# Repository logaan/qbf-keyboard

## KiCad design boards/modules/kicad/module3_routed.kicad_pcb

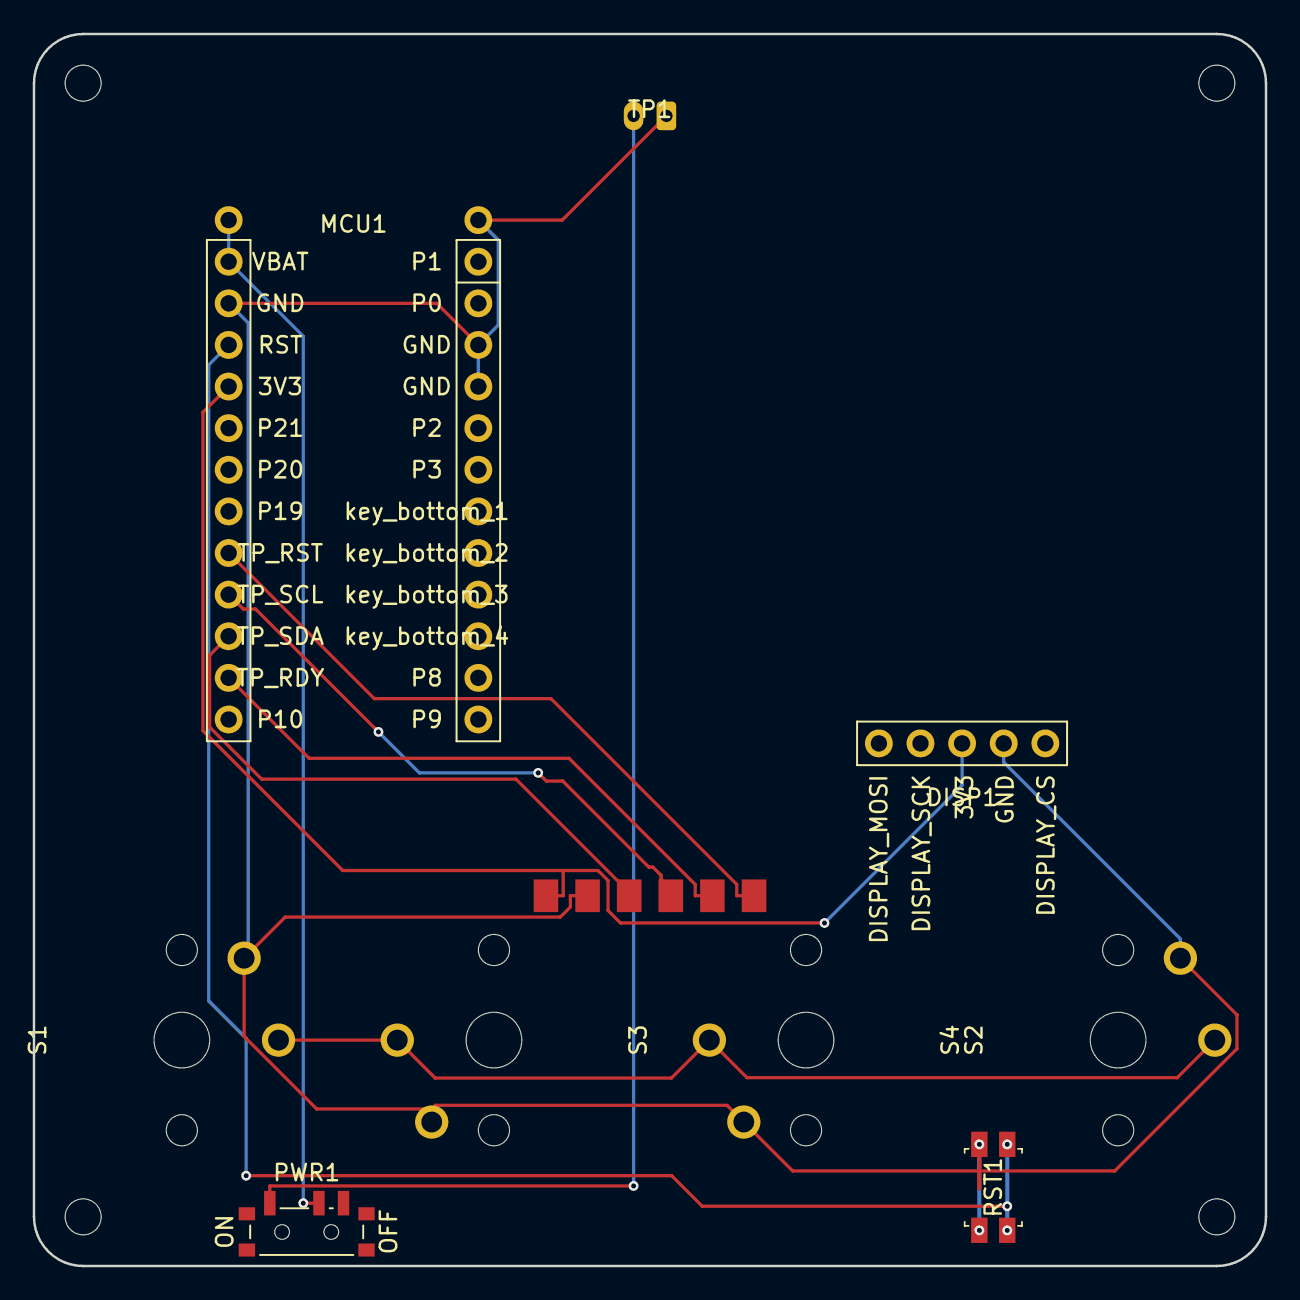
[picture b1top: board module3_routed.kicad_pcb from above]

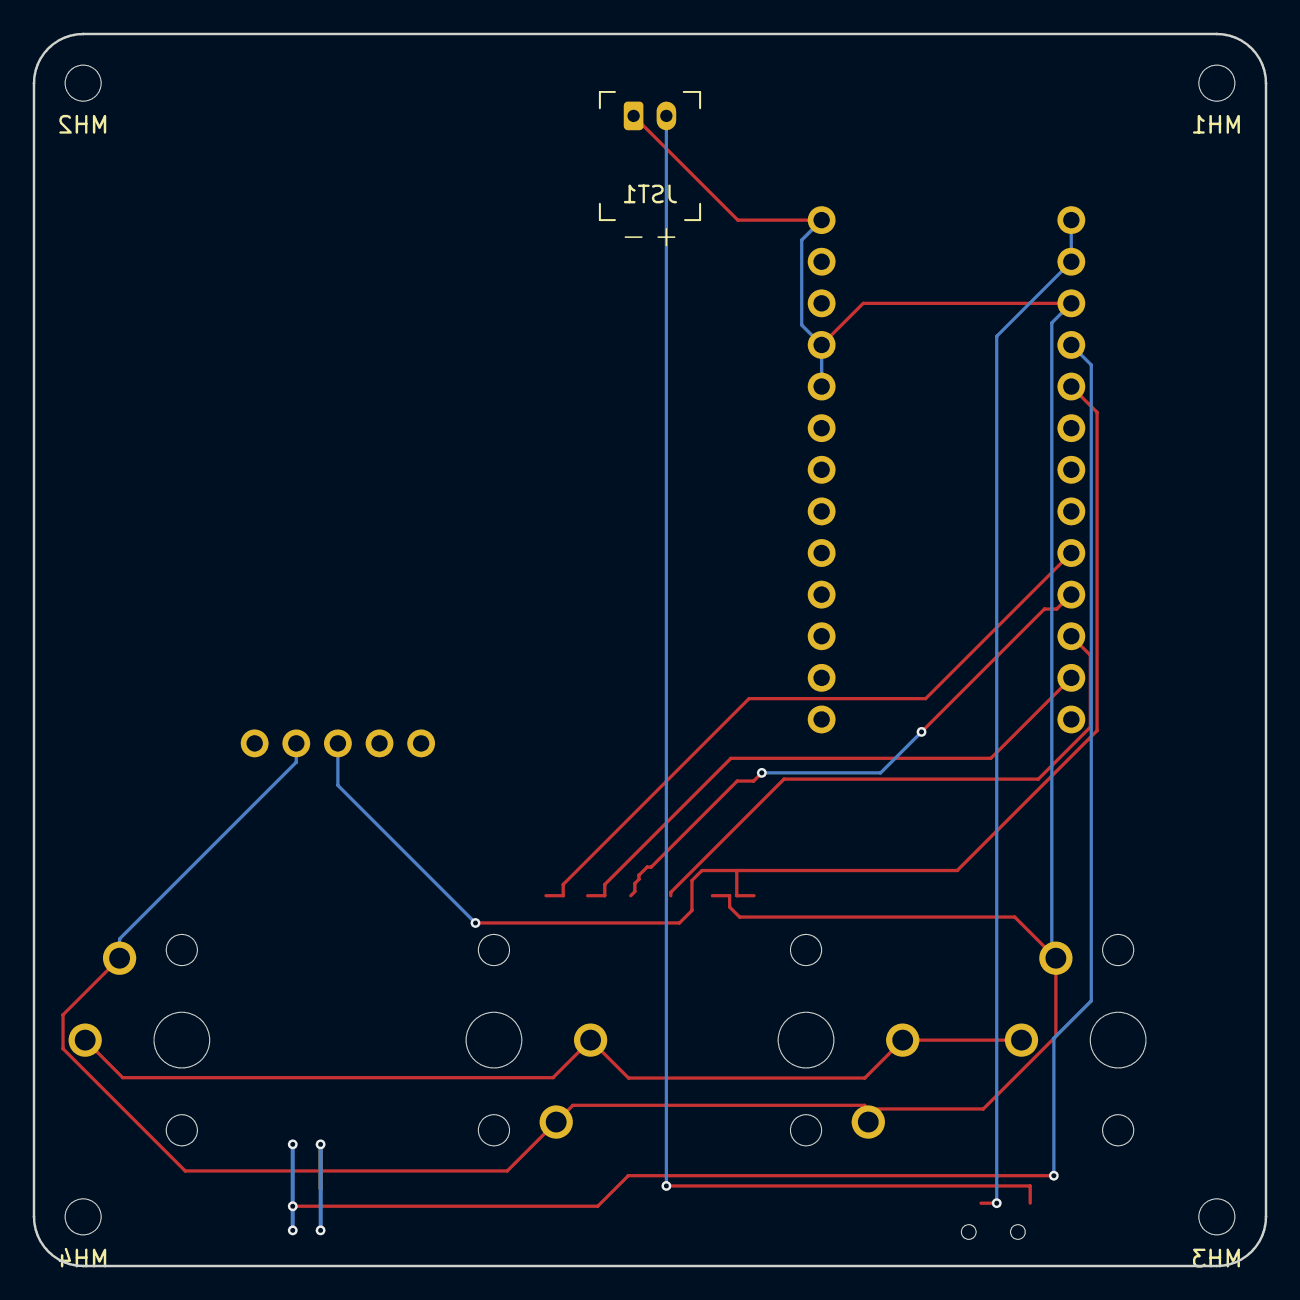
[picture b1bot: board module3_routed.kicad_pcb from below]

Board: 2 copper layers, 75.2 x 75.2 mm, 14 parts (5 on the bottom side), 10 nets.

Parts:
DISP1: display_nice_view
JST1: battery_connector_jst_ph_2
MCU1: mcu_nice_nano
MH1, MH2, MH3, MH4: mounting_hole_npth
PWR1: power_switch_smd_side
RST1: reset_switch_smd_side
S1, S2, S3, S4: switch_choc_v1_v2
TP1: TPS43_abstract_interface

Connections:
3V3: DISP1.3, MCU1.21, TP1.1
BAT_P: JST1.2, PWR1.1
GND: DISP1.4, JST1.1, MCU1.3, MCU1.4, MCU1.23, MCU1.26, RST1.1, RST1.3, S1.1, S2.1, S3.1, S4.1, TP1.2
RST: MCU1.22, RST1.2, RST1.4
TP_RDY: MCU1.14, TP1.5
TP_RST: MCU1.17, TP1.6
TP_SCL: MCU1.16, TP1.4
TP_SDA: MCU1.15, TP1.3
VBAT: MCU1.24, MCU1.25, PWR1.2
default_default: S1.2, S2.2, S3.2, S4.2

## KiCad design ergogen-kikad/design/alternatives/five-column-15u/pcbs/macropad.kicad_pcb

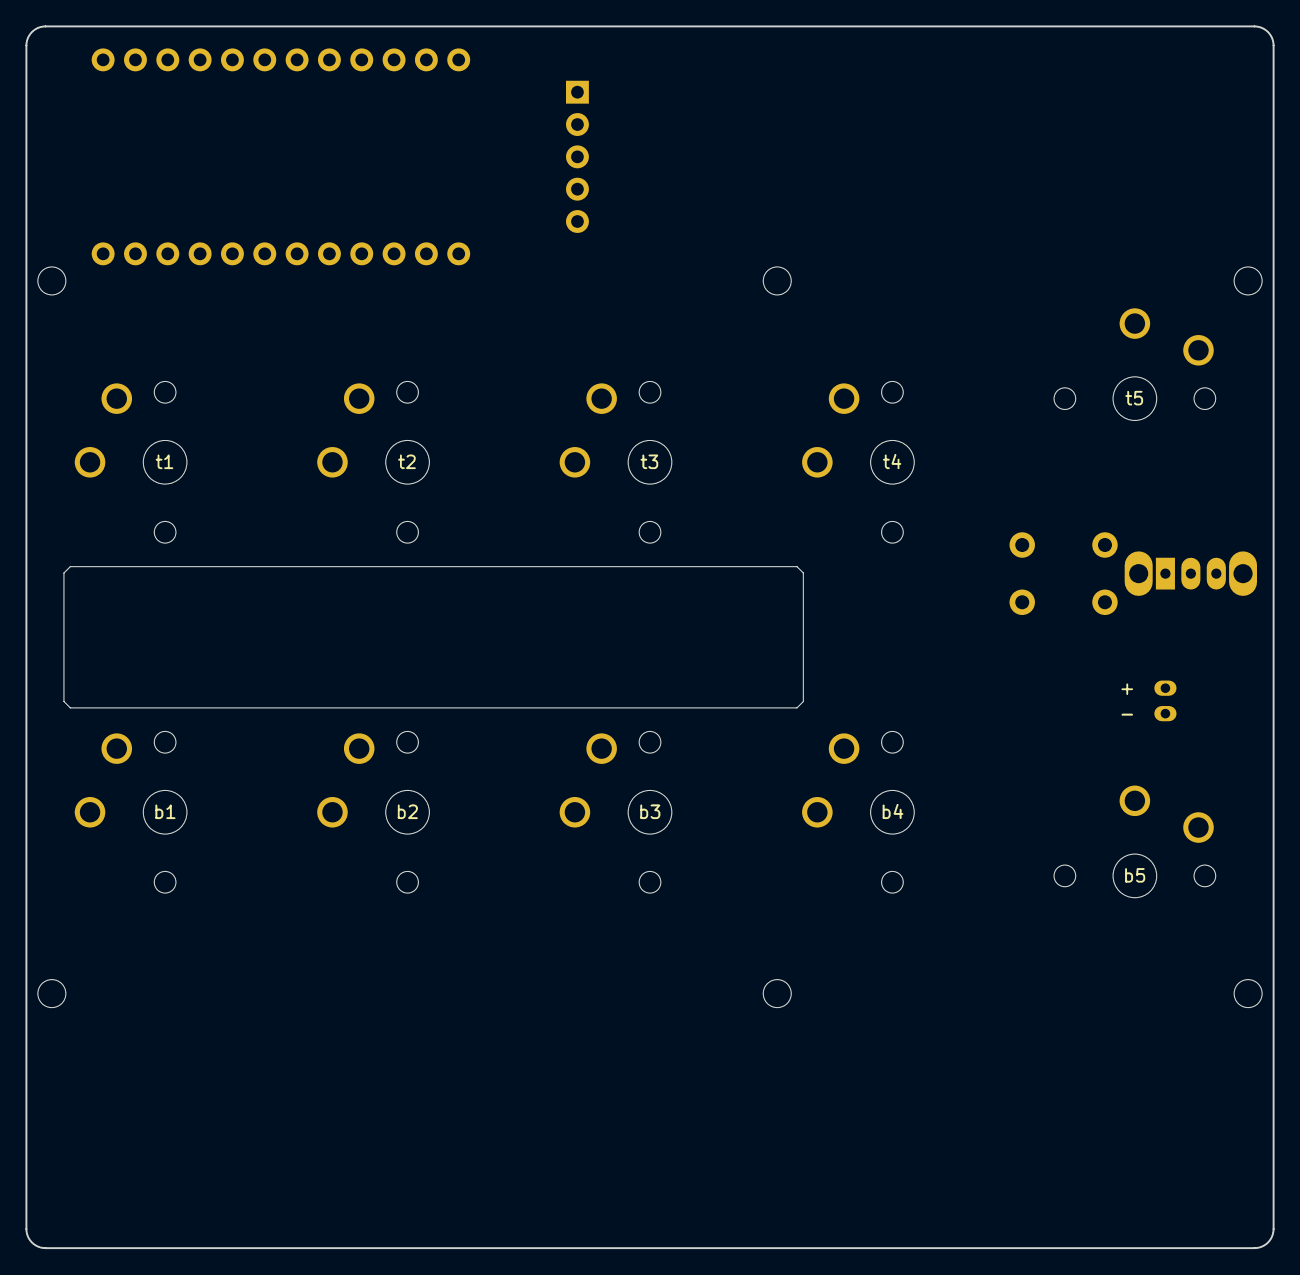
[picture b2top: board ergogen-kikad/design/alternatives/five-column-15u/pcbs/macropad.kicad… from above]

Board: 2 copper layers, 98.0 x 96.0 mm, 23 parts (0 on the bottom side), 18 nets, no tracks yet.

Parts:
BAT1: 301055 220mAh max 57.5x10.5x3.5 z=-1.4; Protected_301055_Battery_Envelope
H1, H2, H3, H4, H5, H6: M2 mount; M2_Mount
J1: JST-PH S2B-PH-K-S; JST_PH_S2B_PH_K_Horizontal
LCD1: nice!view; Nice_View_Socketed_Module
MCU1: nice!nano v2; Nice_Nano_V2
PWR1: OS102011MS2QN1; CK_OS102011MS2QN1
RST1: 6mm top-actuated tactile; SW_PUSH_6mm_H4_3mm
S1, S2, S3, S4, S5, S6, S7, S8: Choc v1 1.5U; PG1350_1_5U
S9, S10: Choc v1 1U; PG1350_1U
WELL1: Battery well 58.1x11.1; Battery_Well

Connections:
3V3: LCD1.3, MCU1.21
BAT_POS: J1.1, PWR1.1
GND: J1.2, LCD1.4, MCU1.3, MCU1.4, MCU1.23, RST1.2, S1.1, S2.1, S3.1, S4.1, S5.2, S6.2, S7.2, S8.2, S9.1, S10.2
LCD_CLK: LCD1.2, MCU1.6
LCD_CS: LCD1.5, MCU1.1
LCD_SI: LCD1.1, MCU1.5
P4: MCU1.7, S1.2
P5: MCU1.8, S2.2
P6: MCU1.9, S3.2
P7: MCU1.10, S4.2
P8: MCU1.11, S9.2
P9: MCU1.12, S5.1
P10: MCU1.13, S6.1
P14: MCU1.15, S8.1
P15: MCU1.16, S10.1
P16: MCU1.14, S7.1
RST: MCU1.22, RST1.1
VBAT: MCU1.24, PWR1.2

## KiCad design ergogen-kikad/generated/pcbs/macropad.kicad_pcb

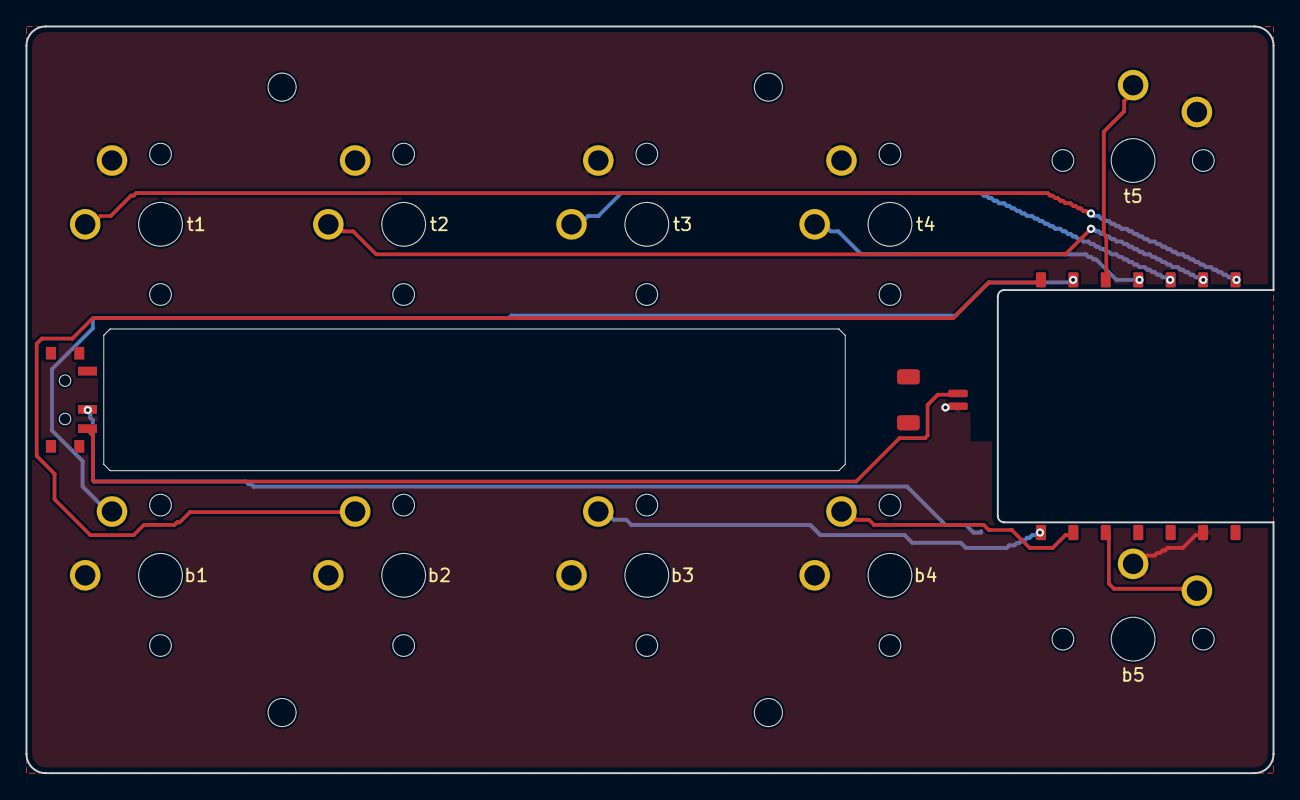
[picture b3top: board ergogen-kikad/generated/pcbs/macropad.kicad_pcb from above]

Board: 2 copper layers, 97.7 x 58.5 mm, 20 parts (1 on the bottom side), 13 nets.

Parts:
BAT1: 301055 220mAh max 57.5x10.5x3.5 z=-1.4; Protected_301055_Battery_Envelope
BW1: Insulated lead to XIAO BAT+ underside; XIAO_Underside_BAT_Wire_Landing
H1, H2, H3, H4: M2 mount; M2_Mount
J1: JST-SH 2-pin horizontal; JST_SH_SM02B_SRSS_TB_Horizontal
MCU1: XIAO nRF52840 Plus edge-soldered; XIAO_nRF52840_Plus_Coplanar_Edge_Solder
PWR1: PCM12SMTR side power; CK_PCM12SMTR
S1, S2, S3, S4, S5, S6, S7, S8: Choc v1 1.5U; PG1350_1_5U
S9, S10: Choc v1 1U; PG1350_1U
WELL1: Battery well 58.1x11.1; Battery_Well

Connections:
BAT_POS: J1.1, PWR1.3
D0: MCU1.1, S1.2
D1: MCU1.2, S2.2
D2: MCU1.3, S3.2
D3: MCU1.4, S4.2
D4: MCU1.5, S9.2
D5: MCU1.6, S5.1
D6: MCU1.7, S6.1
D7: MCU1.8, S7.1
D8: MCU1.9, S8.1
D9: MCU1.10, S10.1
GND: J1.2, MCU1.13, S1.1, S2.1, S3.1, S4.1, S5.2, S6.2, S7.2, S8.2, S9.1, S10.2
VBAT: BW1.1, PWR1.2

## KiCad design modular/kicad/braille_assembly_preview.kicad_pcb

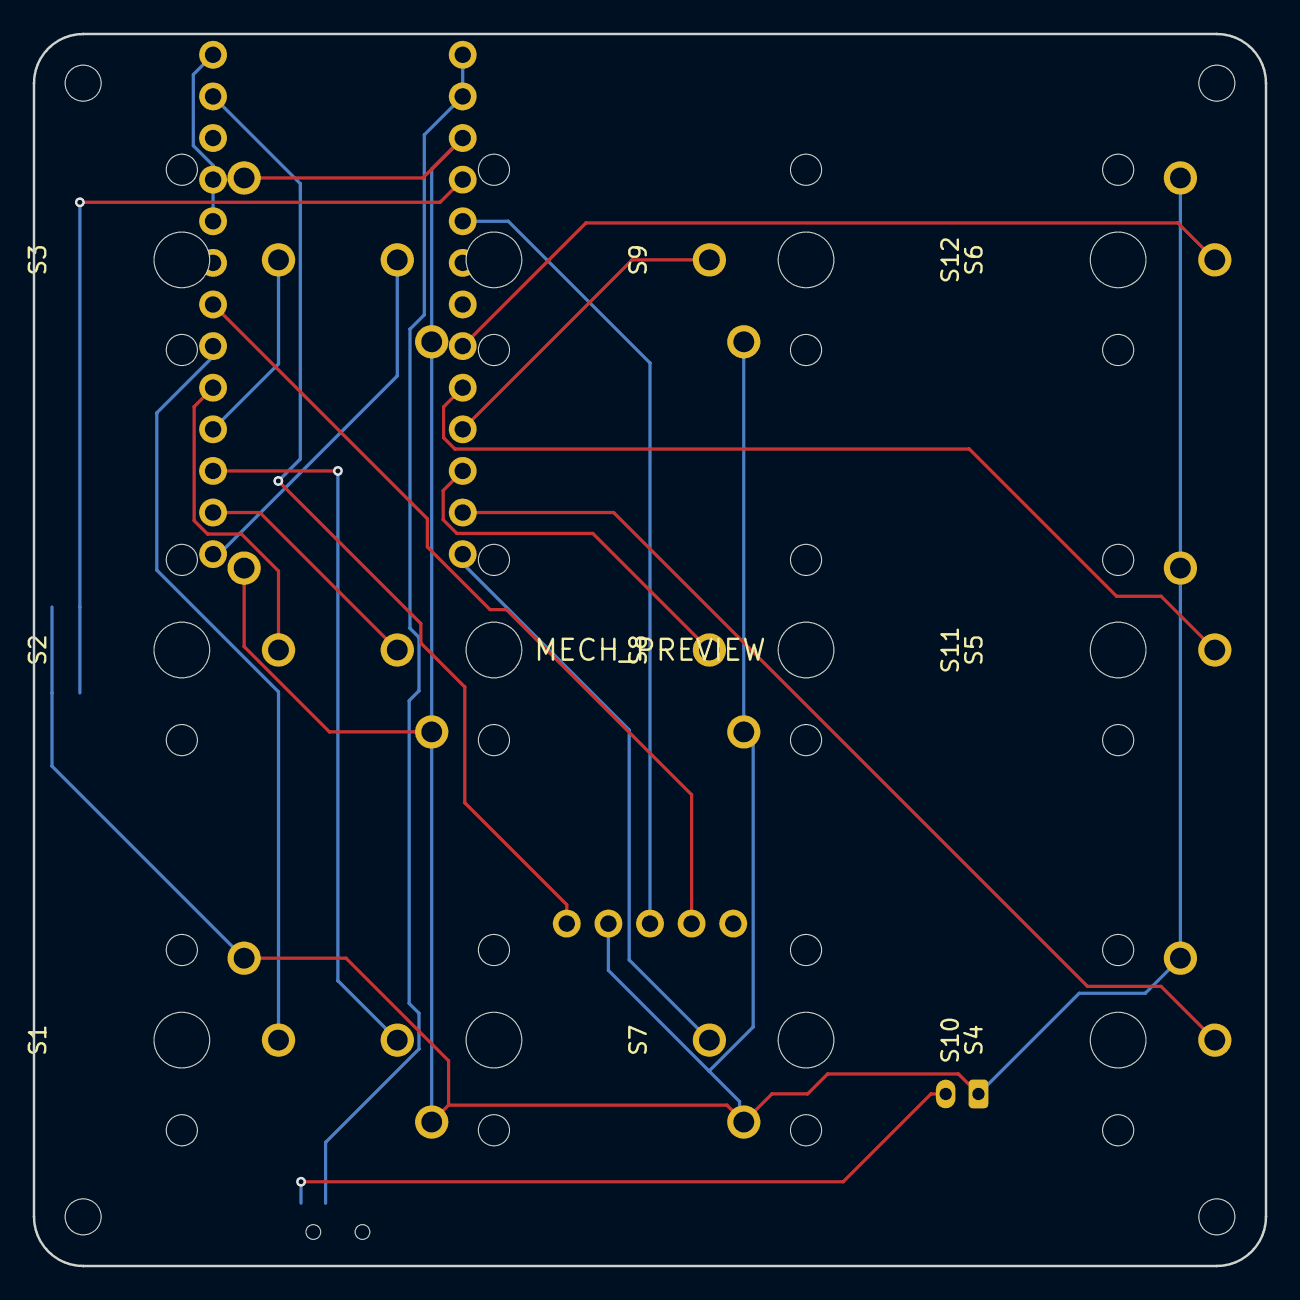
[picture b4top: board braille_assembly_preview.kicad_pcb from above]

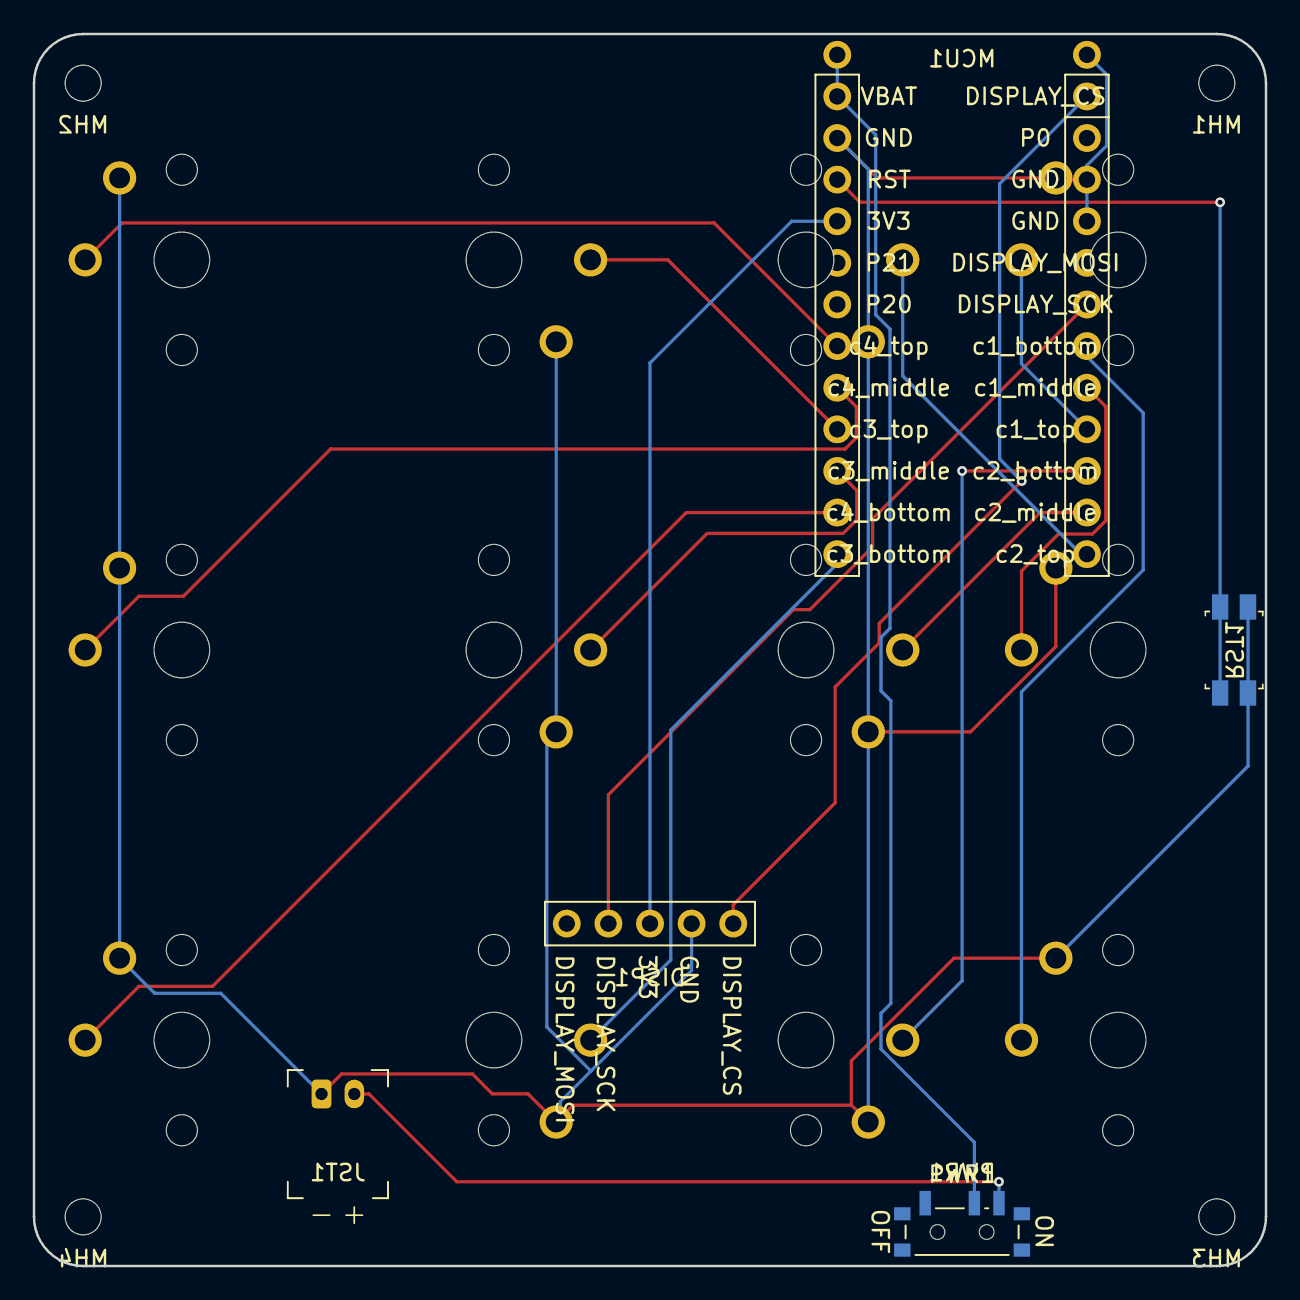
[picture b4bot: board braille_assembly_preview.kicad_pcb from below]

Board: 2 copper layers, 75.2 x 75.2 mm, 22 parts (9 on the bottom side), 20 nets.

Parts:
DISP1: display_nice_view
JST1: battery_connector_jst_ph_2
MCU1: mcu_nice_nano
MECH_PREVIEW: REVIEW_ENVELOPES_ONLY
MH1, MH2, MH3, MH4: mounting_hole_npth
PWR1: power_switch_smd_side
RST1: reset_switch_smd_side
S1, S2, S3, S4, S5, S6, S7, S8, S9, S10, S11, S12: switch_choc_v1_v2

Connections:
3V3: DISP1.3, MCU1.4
BAT_P: JST1.2, PWR1.3
DISPLAY_CS: DISP1.1, MCU1.24
DISPLAY_MOSI: DISP1.5, MCU1.20
DISPLAY_SCK: DISP1.4, MCU1.19
GND: DISP1.2, JST1.1, MCU1.2, MCU1.21, MCU1.22, MCU1.25, RST1.1, RST1.3, S1.1, S2.1, S3.1, S4.1, S5.1, S6.1, S7.1, S8.1, S9.1, S10.1, S11.1, S12.1
RST: MCU1.3, RST1.2, RST1.4
VBAT: MCU1.1, MCU1.26, PWR1.2
c1_bottom: MCU1.18, S1.2
c1_middle: MCU1.17, S2.2
c1_top: MCU1.16, S3.2
c2_bottom: MCU1.15, S7.2
c2_middle: MCU1.14, S8.2
c2_top: MCU1.13, S9.2
c3_bottom: MCU1.12, S10.2
c3_middle: MCU1.10, S11.2
c3_top: MCU1.9, S12.2
c4_bottom: MCU1.11, S4.2
c4_middle: MCU1.8, S5.2
c4_top: MCU1.7, S6.2
